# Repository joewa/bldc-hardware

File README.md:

bldc-hardware
=============

This the Hardware for my open source custom ESC. This is a forked repository from mrkindustries, who made many improvements to my original hardware design.

Here is a BOM on google drive that I try to keep up to date:
https://docs.google.com/spreadsheet/ccc?key=0AnvZ-ouEB058dGpzaDl4MUxNM3NxZ1BzTWNZZ1RhRUE&usp=sharing

Have a look at this post for a tutorial on how to get started:
http://vedder.se/2015/01/vesc-open-source-esc/

VESC Hardware is licensed under the Creative Commons Attribution-ShareAlike 4.0 International License. To view a copy of this license, visit http://creativecommons.org/licenses/by-sa/4.0/.

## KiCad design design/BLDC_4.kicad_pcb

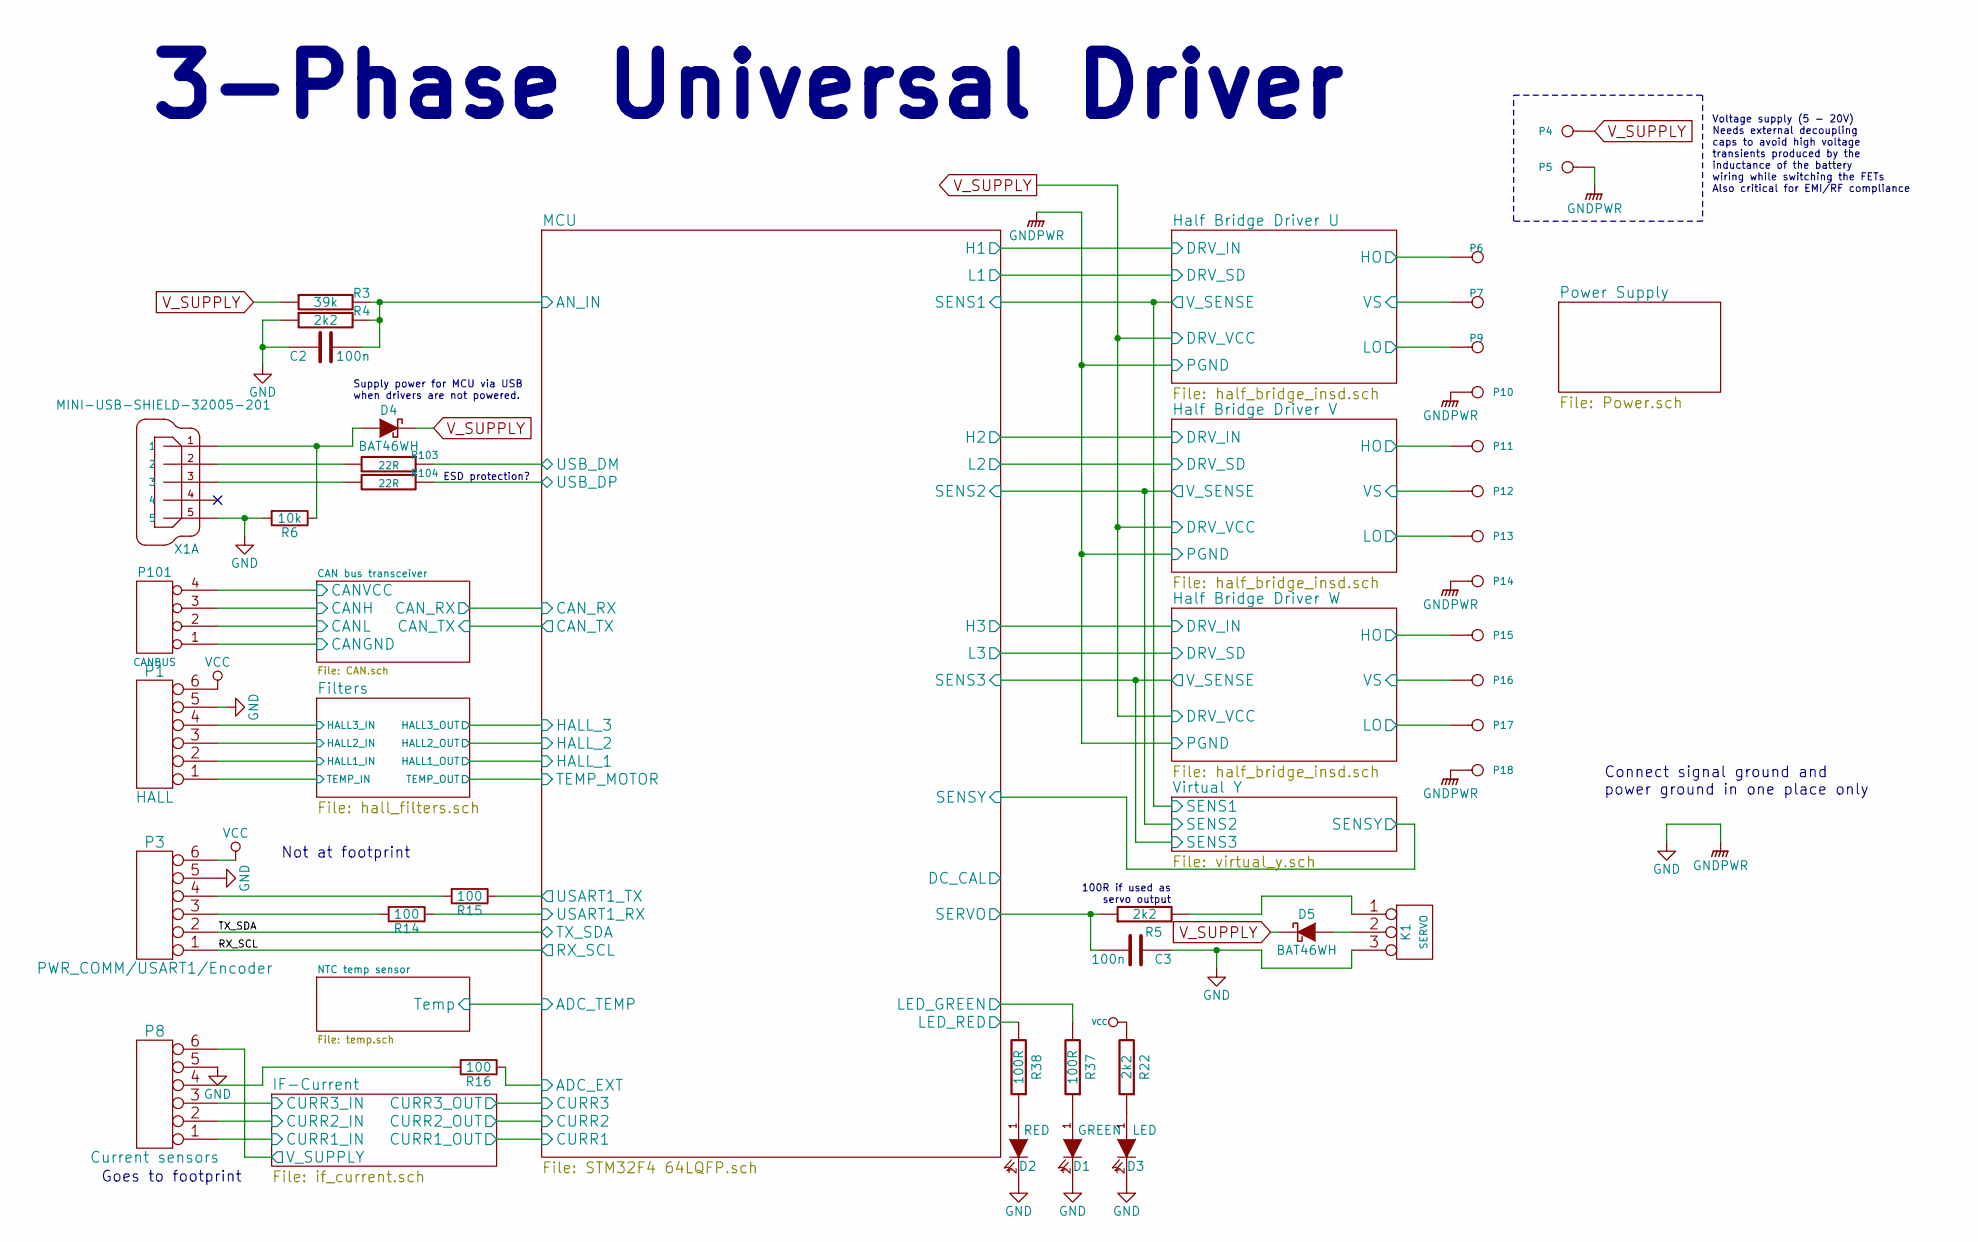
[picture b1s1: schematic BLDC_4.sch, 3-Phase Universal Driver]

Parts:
C2, C3: 100n; C_0603
D1: GREEN; LED-0603
D2: RED; LED-0603
D3: LED; LED-0603
D4, D5: BAT46WH; SOD-123
K1: SERVO; pinhead-1X03
P1: HALL; MICRO_JST_6
P3: PWR_COMM/USART1/Encoder; MICRO_JST_6
P4: IN+; 1PAD_4x5mm
P5: IN-; 1PAD_4x5mm
P6, P7: CONN_DRV; 1PAD_4x5mm
P8: Current sensors; MICRO_JST_6
P9, P10, P11, P12, P13, P14, P15, P16, P17, P18: CONN_DRV; PAD_DRV
P101: CANBUS; pinhead-1X03
R3: 39k; R_0603_HandSoldering
R4, R5, R22: 2k2; R_0603_HandSoldering
R6: 10k; R_0603
R14, R15, R16: 100; R_0603
R37, R38: 100R; R_0603
R103, R104: 22R; R_0603
X1: MINI-USB-SHIELD-32005-201; con-cypressindustries-32005-201

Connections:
/CAN bus transceiver/CANGND: P101.1; also elsewhere on the board
/CAN bus transceiver/CANH: P101.3; also elsewhere on the board
/CAN bus transceiver/CANL: P101.2; also elsewhere on the board
/Filters/HALL1_IN: P1.2; also elsewhere on the board
/Filters/HALL2_IN: P1.3; also elsewhere on the board
/Filters/HALL3_IN: P1.4; also elsewhere on the board
/Filters/TEMP_IN: P1.1; also elsewhere on the board
/Half Bridge Driver U/HO: P6.1; also elsewhere on the board
/Half Bridge Driver U/LO: P9.1; also elsewhere on the board
/Half Bridge Driver U/VS: P7.1; also elsewhere on the board
/Half Bridge Driver V/HO: P11.1; also elsewhere on the board
/Half Bridge Driver V/LO: P13.1; also elsewhere on the board
/Half Bridge Driver V/VS: P12.1; also elsewhere on the board
/Half Bridge Driver W/HO: P15.1; also elsewhere on the board
/Half Bridge Driver W/LO: P17.1; also elsewhere on the board
/Half Bridge Driver W/VS: P16.1; also elsewhere on the board
/IF-Current/CURR1_IN: P8.1; also elsewhere on the board
/IF-Current/CURR2_IN: P8.2; also elsewhere on the board
/IF-Current/CURR3_IN: P8.3; also elsewhere on the board
/IF-Current/V_SUPPLY: P8.6; also elsewhere on the board
/MCU/ADC_EXT: R16.1; also elsewhere on the board
/MCU/AN_IN: C2.2, R3.2, R4.2; also elsewhere on the board
/MCU/LED_GREEN: R37.2; also elsewhere on the board
/MCU/LED_RED: R38.2; also elsewhere on the board
/MCU/RX_SCL: P3.1; also elsewhere on the board
/MCU/SERVO: C3.2, R5.1; also elsewhere on the board
/MCU/TX_SDA: P3.2; also elsewhere on the board
/MCU/USART1_RX: R14.1; also elsewhere on the board
/MCU/USART1_TX: R15.1; also elsewhere on the board
/MCU/USB_DM: R103.1; also elsewhere on the board
/MCU/USB_DP: R104.1; also elsewhere on the board
GND: C2.1, C3.1, D1.2 (K), D2.2 (K), D3.2 (K), K1.3, P1.5, P3.5, P5.1, P8.5, P10.1, P14.1, P18.1, R4.1, R6.2, X1.5; also elsewhere on the board
unnamed: D1.1 (A), R37.1
unnamed: D2.1 (A), R38.1
unnamed: D3.1 (A), R22.1
unnamed: D4.2 (A), R6.1, X1.1
unnamed: D5.2 (A), K1.2 (PM)
unnamed: K1.1, R5.2
unnamed: P3.3, R14.2
unnamed: P3.4, R15.2
unnamed: P8.4, R16.2
unnamed: R103.2, X1.2
unnamed: R104.2, X1.3
VCC: P1.6, P3.6, R22.2; also elsewhere on the board
V_SUPPLY: D4.1 (K), D5.1 (K), P4.1, R3.1; also elsewhere on the board

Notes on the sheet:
100R if used as servo output
Supply power for MCU via USB when drivers are not powered.
ESD protection?
3-Phase Universal Driver
Voltage supply (5 - 20V) Needs external decoupling caps to avoid high voltage transients produced by the inductance of the battery wiring while switching the FETs Also critical for EMI/RF compliance
Connect signal ground and power ground in one place only
Not at footprint
Goes to footprint

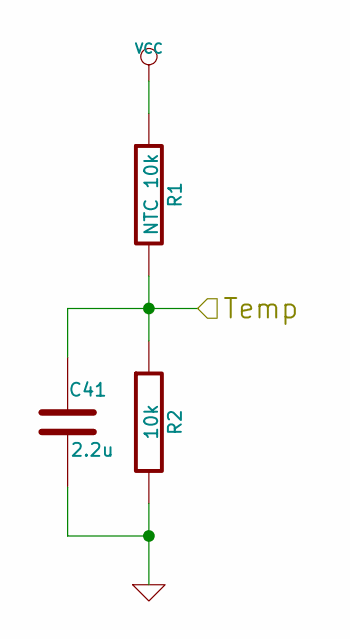
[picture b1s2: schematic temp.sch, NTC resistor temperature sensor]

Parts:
C41: 2.2u; C_0603
R1: NTC 10k; R_0603_HandSoldering
R2: 10k; R_0603_HandSoldering

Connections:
/MCU/ADC_TEMP: C41.1, R1.2, R2.1; also elsewhere on the board
GND: C41.2, R2.2; also elsewhere on the board
VCC: R1.1; also elsewhere on the board

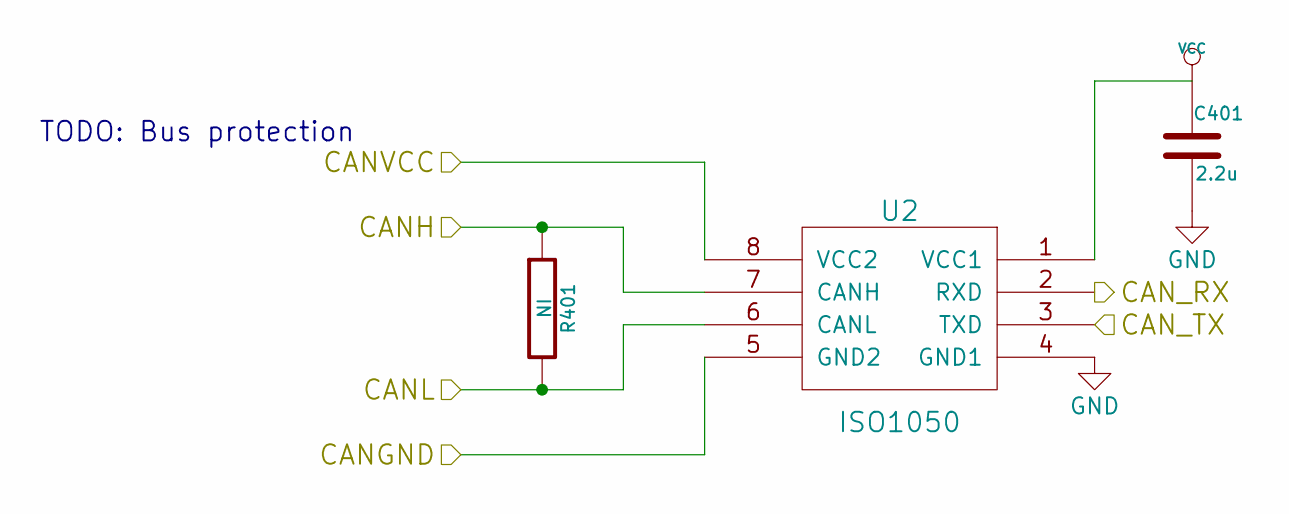
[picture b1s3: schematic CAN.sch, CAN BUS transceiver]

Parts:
C401: 2.2u; C_0603
R401: NI; R_0603_HandSoldering
U2: ISO1050; PDSO-G8

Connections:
/CAN bus transceiver/CANGND: U2.5 (GND2); also elsewhere on the board
/CAN bus transceiver/CANH: R401.1, U2.7 (CANH); also elsewhere on the board
/CAN bus transceiver/CANL: R401.2, U2.6 (CANL); also elsewhere on the board
/CAN bus transceiver/CAN_RX: U2.2 (RXD); also elsewhere on the board
/CAN bus transceiver/CAN_TX: U2.3 (TXD); also elsewhere on the board
GND: C401.2, U2.4 (GND1); also elsewhere on the board
VCC: C401.1, U2.1 (VCC1); also elsewhere on the board

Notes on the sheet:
TODO: Bus protection

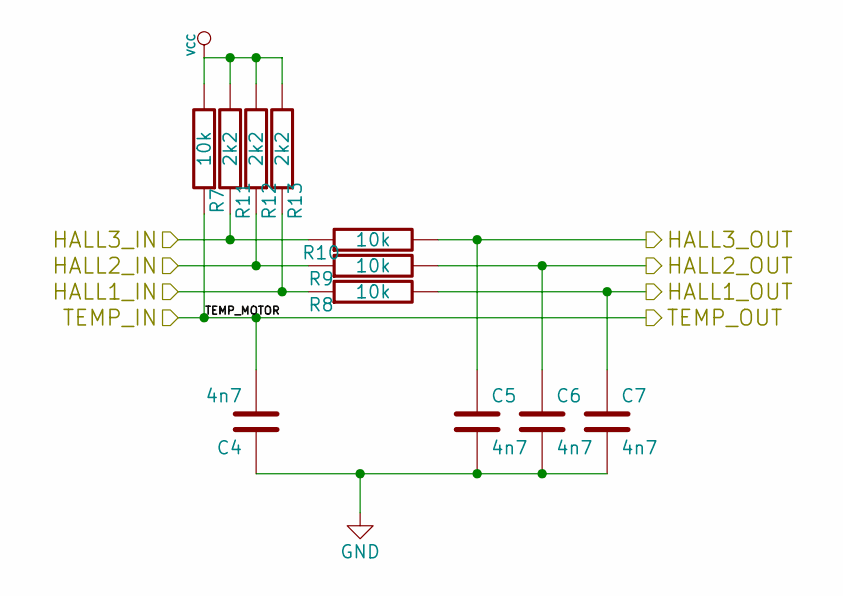
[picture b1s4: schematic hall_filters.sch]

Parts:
C4, C5, C6, C7: 4n7; C_0603
R7, R8, R9, R10: 10k; R_0603
R11, R12, R13: 2k2; R_0603

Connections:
/Filters/HALL1_IN: R8.1, R13.1; also elsewhere on the board
/Filters/HALL1_OUT: C7.1, R8.2; also elsewhere on the board
/Filters/HALL2_IN: R9.1, R12.1; also elsewhere on the board
/Filters/HALL2_OUT: C6.1, R9.2; also elsewhere on the board
/Filters/HALL3_IN: R10.1, R11.1; also elsewhere on the board
/Filters/HALL3_OUT: C5.1, R10.2; also elsewhere on the board
/Filters/TEMP_IN: C4.2, R7.1; also elsewhere on the board
GND: C4.1, C5.2, C6.2, C7.2; also elsewhere on the board
VCC: R7.2, R11.2, R12.2, R13.2; also elsewhere on the board

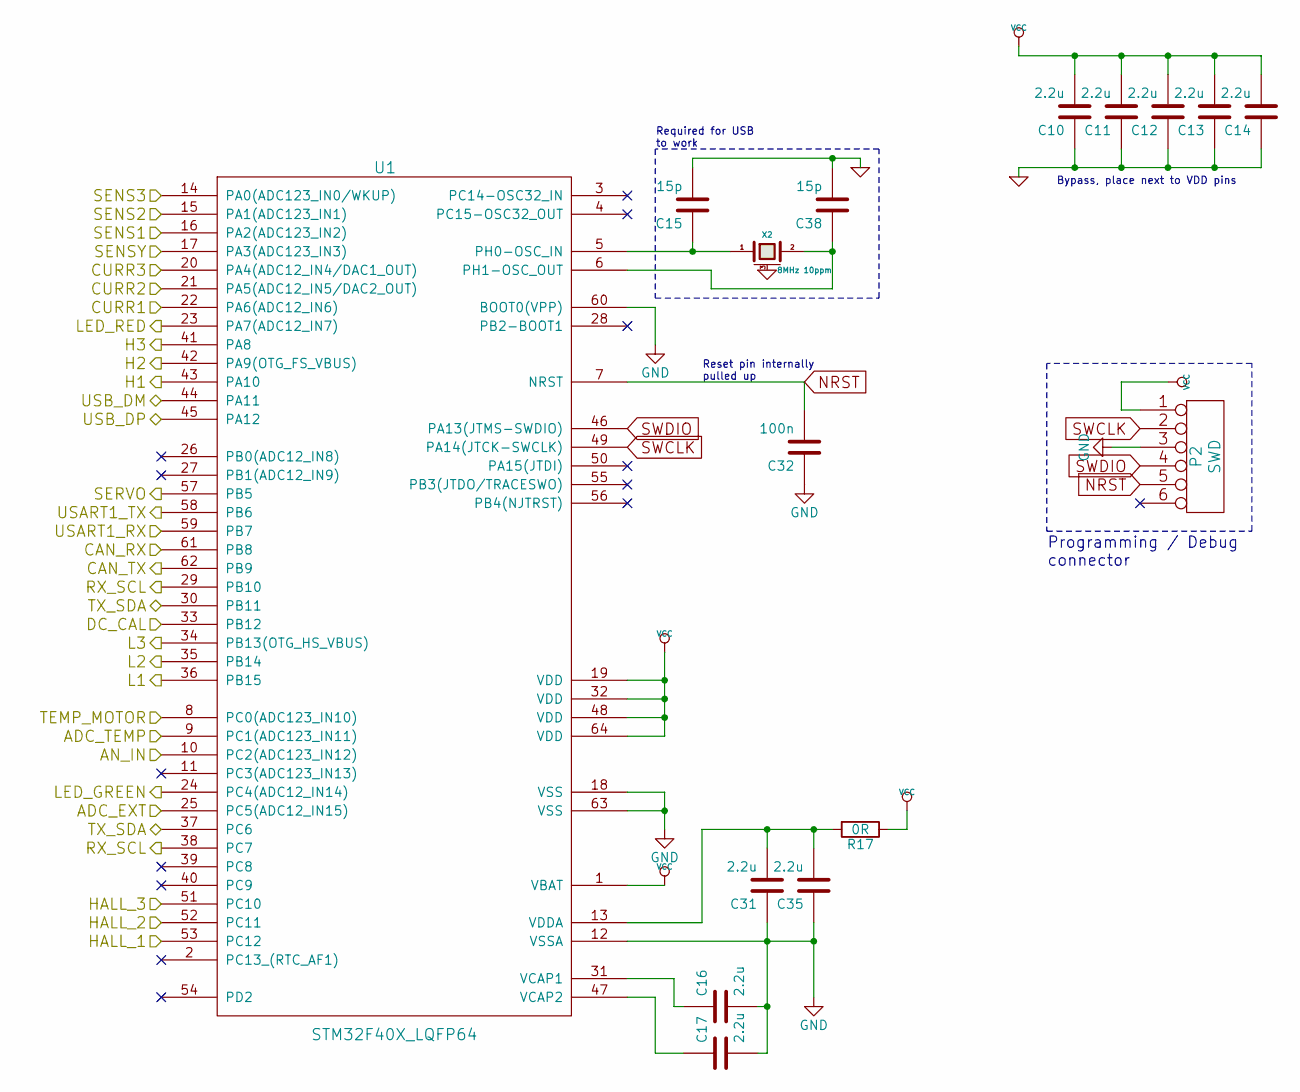
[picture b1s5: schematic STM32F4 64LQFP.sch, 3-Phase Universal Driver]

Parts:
C10, C11, C12, C13, C14, C16, C17, C31, C35: 2.2u; C_0603
C15, C38: 15p; C_0603
C32: 100n; C_0603
P2: SWD; MICRO_JST_6
R17: 0R; R_0603_HandSoldering
U1: STM32F40X_LQFP64; lqfp64_pad_mod
X2: 8MHz 10ppm; Crystal_5x3mm; mfg# ABM3B-8.0-10-1UT

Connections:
/CAN bus transceiver/CAN_RX: U1.61 (PB8); also elsewhere on the board
/CAN bus transceiver/CAN_TX: U1.62 (PB9); also elsewhere on the board
/Filters/HALL1_OUT: U1.53 (PC12); also elsewhere on the board
/Filters/HALL2_OUT: U1.52 (PC11); also elsewhere on the board
/Filters/HALL3_OUT: U1.51 (PC10); also elsewhere on the board
/Filters/TEMP_IN: U1.8 (PC0(ADC123_IN10)); also elsewhere on the board
/Half Bridge Driver U/DRV_IN: U1.43 (PA10); also elsewhere on the board
/Half Bridge Driver U/DRV_SD: U1.36 (PB15); also elsewhere on the board
/Half Bridge Driver V/DRV_IN: U1.42 (PA9(OTG_FS_VBUS)); also elsewhere on the board
/Half Bridge Driver V/DRV_SD: U1.35 (PB14); also elsewhere on the board
/Half Bridge Driver W/DRV_IN: U1.41 (PA8); also elsewhere on the board
/Half Bridge Driver W/DRV_SD: U1.34 (PB13(OTG_HS_VBUS)); also elsewhere on the board
/MCU/ADC_EXT: U1.25 (PC5(ADC12_IN15)); also elsewhere on the board
/MCU/ADC_TEMP: U1.9 (PC1(ADC123_IN11)); also elsewhere on the board
/MCU/AN_IN: U1.10 (PC2(ADC123_IN12)); also elsewhere on the board
/MCU/CURR1: U1.22 (PA6(ADC12_IN6)); also elsewhere on the board
/MCU/CURR2: U1.21 (PA5(ADC12_IN5/DAC2_OUT)); also elsewhere on the board
/MCU/CURR3: U1.20 (PA4(ADC12_IN4/DAC1_OUT)); also elsewhere on the board
/MCU/LED_GREEN: U1.24 (PC4(ADC12_IN14)); also elsewhere on the board
/MCU/LED_RED: U1.23 (PA7(ADC12_IN7)); also elsewhere on the board
/MCU/RX_SCL: U1.29 (PB10), U1.38 (PC7); also elsewhere on the board
/MCU/SENS1: U1.16 (PA2(ADC123_IN2)); also elsewhere on the board
/MCU/SENS2: U1.15 (PA1(ADC123_IN1)); also elsewhere on the board
/MCU/SENS3: U1.14 (PA0(ADC123_IN0/WKUP)); also elsewhere on the board
/MCU/SENSY: U1.17 (PA3(ADC123_IN3)); also elsewhere on the board
/MCU/SERVO: U1.57 (PB5); also elsewhere on the board
/MCU/TX_SDA: U1.30 (PB11), U1.37 (PC6); also elsewhere on the board
/MCU/USART1_RX: U1.59 (PB7); also elsewhere on the board
/MCU/USART1_TX: U1.58 (PB6); also elsewhere on the board
/MCU/USB_DM: U1.44 (PA11); also elsewhere on the board
/MCU/USB_DP: U1.45 (PA12); also elsewhere on the board
GND: C10.1, C11.1, C12.1, C13.1, C14.1, C15.2, C16.2, C17.2, C31.1, C32.1, C35.1, C38.2, P2.3, U1.12 (VSSA), U1.18 (VSS), U1.60 (BOOT0(VPP)), U1.63 (VSS), X2.3 (case); also elsewhere on the board
NRST: C32.2, P2.5, U1.7 (NRST)
unnamed: C15.1, U1.5 (PH0-OSC_IN), X2.1
unnamed: C16.1, U1.31 (VCAP1)
unnamed: C17.1, U1.47 (VCAP2)
unnamed: C31.2, C35.2, R17.2, U1.13 (VDDA)
unnamed: C38.1, U1.6 (PH1-OSC_OUT), X2.2
SWCLK: P2.2, U1.49 (PA14(JTCK-SWCLK))
SWDIO: P2.4, U1.46 (PA13(JTMS-SWDIO))
VCC: C10.2, C11.2, C12.2, C13.2, C14.2, P2.1, R17.1, U1.1 (VBAT), U1.19 (VDD), U1.32 (VDD), U1.48 (VDD), U1.64 (VDD); also elsewhere on the board

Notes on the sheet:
Programming / Debug connector
Reset pin internally pulled up
Required for USB to work
Bypass, place next to VDD pins

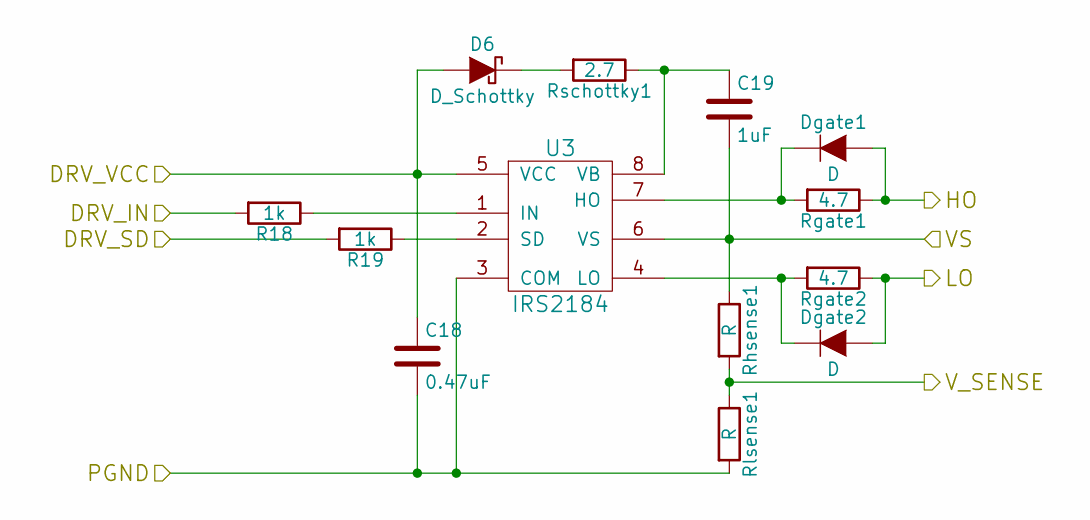
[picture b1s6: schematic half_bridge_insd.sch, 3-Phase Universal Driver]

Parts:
C18: 0.47uF; C_0805_HandSoldering
C19: 1uF; C_1210_HandSoldering
D6: D_Schottky; DO-214AC_SOD-123
Dgate1, Dgate2: D; SOD-123
R18, R19: 1k; R_0603
Rgate1, Rgate2: 4.7; R_0805_HandSoldering
Rhsense1: R; R_0805_HandSoldering
Rlsense1: R; R_0603_HandSoldering
Rschottky1: 2.7; R_0805_HandSoldering
U3: IRS2184; SOIC-8_3.9x4.9mm_Pitch1.27mm

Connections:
/Half Bridge Driver U/DRV_IN: R18.2; also elsewhere on the board
/Half Bridge Driver U/DRV_SD: R19.2; also elsewhere on the board
/Half Bridge Driver U/HO: Dgate1.2 (A), Rgate1.1; also elsewhere on the board
/Half Bridge Driver U/LO: Dgate2.2 (A), Rgate2.1; also elsewhere on the board
/Half Bridge Driver U/VS: C19.2, Rhsense1.1, U3.6 (VS); also elsewhere on the board
/MCU/SENS1: Rhsense1.2, Rlsense1.1; also elsewhere on the board
GND: C18.2, Rlsense1.2, U3.3 (COM); also elsewhere on the board
unnamed: C19.1, Rschottky1.1, U3.8 (VB)
unnamed: D6.1 (K), Rschottky1.2
unnamed: Dgate1.1 (K), Rgate1.2, U3.7 (HO)
unnamed: Dgate2.1 (K), Rgate2.2, U3.4 (LO)
unnamed: R18.1, U3.1 (IN)
unnamed: R19.1, U3.2 (SD)
V_SUPPLY: C18.1, D6.2 (A), U3.5 (VCC); also elsewhere on the board

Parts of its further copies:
C20, C22: 0.47uF; C_0805_HandSoldering
C21, C23: 1uF; C_1210_HandSoldering
D7, D8: D_Schottky; DO-214AC_SOD-123
Dgate3, Dgate4, Dgate5, Dgate6: D; SOD-123
R20, R21, R23, R24: 1k; R_0603
Rgate3, Rgate4, Rgate5, Rgate6: 4.7; R_0805_HandSoldering
Rhsense2, Rhsense3: R; R_0805_HandSoldering
Rlsense2, Rlsense3: R; R_0603_HandSoldering
Rschottky2, Rschottky3: 2.7; R_0805_HandSoldering
U4, U5: IRS2184; SOIC-8_3.9x4.9mm_Pitch1.27mm

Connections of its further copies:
/Half Bridge Driver V/DRV_IN: R20.2; also elsewhere on the board
/Half Bridge Driver V/DRV_SD: R21.2; also elsewhere on the board
/Half Bridge Driver V/HO: Dgate3.2 (A), Rgate3.1; also elsewhere on the board
/Half Bridge Driver V/LO: Dgate4.2 (A), Rgate4.1; also elsewhere on the board
/Half Bridge Driver V/VS: C21.2, Rhsense2.1, U4.6 (VS); also elsewhere on the board
/Half Bridge Driver W/DRV_IN: R23.2; also elsewhere on the board
/Half Bridge Driver W/DRV_SD: R24.2; also elsewhere on the board
/Half Bridge Driver W/HO: Dgate5.2 (A), Rgate5.1; also elsewhere on the board
/Half Bridge Driver W/LO: Dgate6.2 (A), Rgate6.1; also elsewhere on the board
/Half Bridge Driver W/VS: C23.2, Rhsense3.1, U5.6 (VS); also elsewhere on the board
/MCU/SENS2: Rhsense2.2, Rlsense2.1; also elsewhere on the board
/MCU/SENS3: Rhsense3.2, Rlsense3.1; also elsewhere on the board
GND: C20.2, C22.2, Rlsense2.2, Rlsense3.2, U4.3 (COM), U5.3 (COM); also elsewhere on the board
unnamed: C21.1, Rschottky2.1, U4.8 (VB)
unnamed: C23.1, Rschottky3.1, U5.8 (VB)
unnamed: D7.1 (K), Rschottky2.2
unnamed: D8.1 (K), Rschottky3.2
unnamed: Dgate3.1 (K), Rgate3.2, U4.7 (HO)
unnamed: Dgate4.1 (K), Rgate4.2, U4.4 (LO)
unnamed: Dgate5.1 (K), Rgate5.2, U5.7 (HO)
unnamed: Dgate6.1 (K), Rgate6.2, U5.4 (LO)
unnamed: R20.1, U4.1 (IN)
unnamed: R21.1, U4.2 (SD)
unnamed: R23.1, U5.1 (IN)
unnamed: R24.1, U5.2 (SD)
V_SUPPLY: C20.1, C22.1, D7.2 (A), D8.2 (A), U4.5 (VCC), U5.5 (VCC); also elsewhere on the board

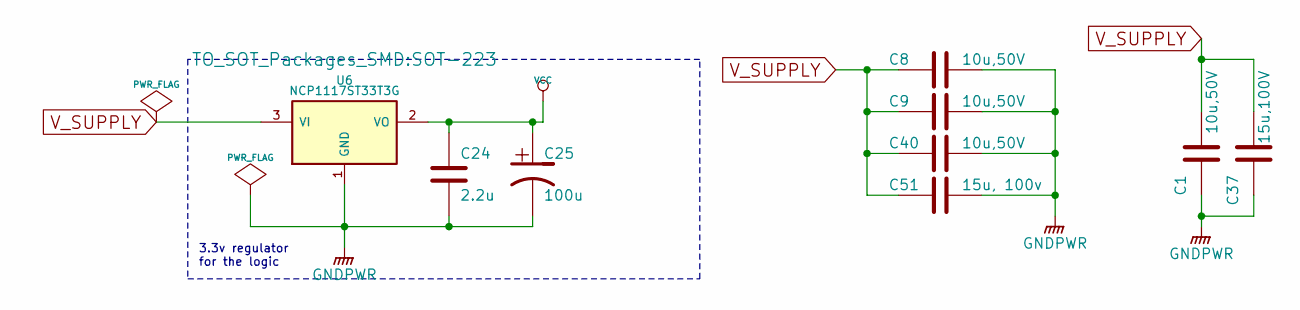
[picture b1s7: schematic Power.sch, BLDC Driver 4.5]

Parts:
C1, C8, C9, C40: 10u,50V; C_1206
C24: 2.2u; C_0603
C25: 100u; TantalC_SizeB_EIA-3528_HandSoldering
C37: 15u,100V; C_2220
C51: 15u, 100v; C_2220
U6: NCP1117ST33T3G; SOT-223

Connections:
GND: C1.1, C8.1, C9.1, C24.2, C25.2, C37.1, C40.1, C51.1, U6.1 (GND); also elsewhere on the board
VCC: C24.1, C25.1, U6.2 (VO); also elsewhere on the board
V_SUPPLY: C1.2, C8.2, C9.2, C37.2, C40.2, C51.2, U6.3 (VI); also elsewhere on the board

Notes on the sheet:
3.3v regulator for the logic

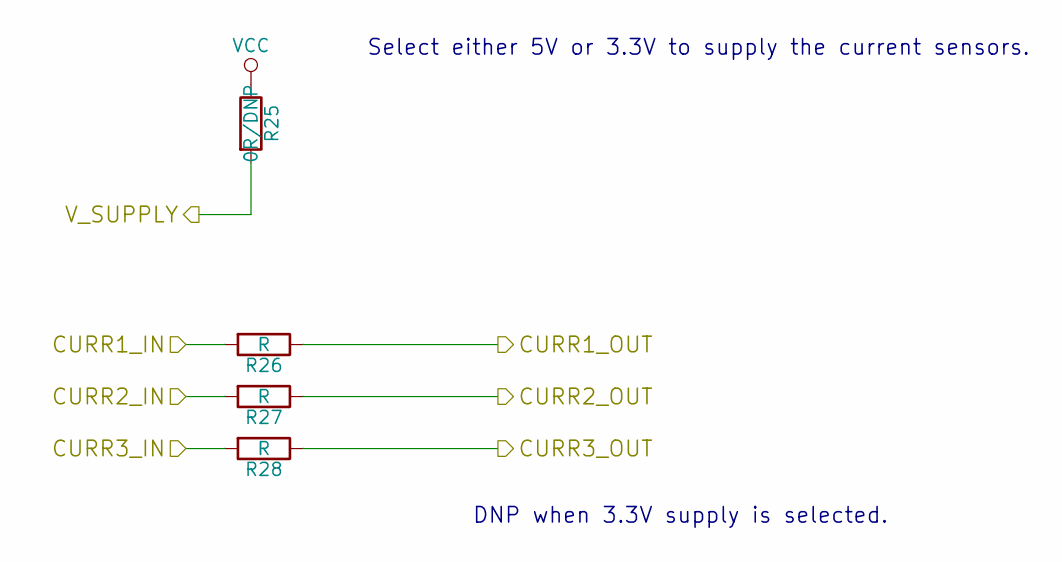
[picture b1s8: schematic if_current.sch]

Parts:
R25: 0R/DNP; R_0603_HandSoldering
R26, R27, R28: R; R_0603

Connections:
/IF-Current/CURR1_IN: R26.2; also elsewhere on the board
/IF-Current/CURR2_IN: R27.2; also elsewhere on the board
/IF-Current/CURR3_IN: R28.2; also elsewhere on the board
/IF-Current/V_SUPPLY: R25.2; also elsewhere on the board
/MCU/CURR1: R26.1; also elsewhere on the board
/MCU/CURR2: R27.1; also elsewhere on the board
/MCU/CURR3: R28.1; also elsewhere on the board
VCC: R25.1; also elsewhere on the board

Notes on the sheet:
Select either 5V or 3.3V to supply the current sensors.
DNP when 3.3V supply is selected.

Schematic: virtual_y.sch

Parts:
R29, R30, R31: R; R_0603_HandSoldering

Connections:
/MCU/SENS1: R29.2; also elsewhere on the board
/MCU/SENS2: R30.2; also elsewhere on the board
/MCU/SENS3: R31.2; also elsewhere on the board
/MCU/SENSY: R29.1, R30.1, R31.1; also elsewhere on the board

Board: 2 copper layers, 127 parts (0 on the bottom side), 90 nets, no tracks yet.

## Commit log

2015-08-22 Saved project with more recent version of KiCad. Added IRS2184 half bridge driver to BLDC_4_cache.lib
2015-08-24 Draft IRS2184 bootstrap driver circuit.
2015-08-24 Added new drivers and removed the big old one.
2015-08-26 Removed 5V power level. Integrated isolated CAN bus driver.
2015-08-27 First complete draft of the schematics.
2015-08-27 Assigned some footprints.
2015-09-02 Added footprint that fits SOD-123 and DO-214AC bootstrap diodes.
2015-09-04 Added Gitter badge
2015-09-04 Selected footprints
2015-09-05 Generated first netlist and started working with pcbnew.
2015-09-23 Arranged some parts.
2015-12-29 Agreed programming connector with esden.
